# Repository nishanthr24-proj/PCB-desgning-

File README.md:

# PCB-desgning-

Solar battery charge controller designed in KiCad, with green charging and red fault LEDs.

The editable project, local libraries, populated 3D assembly, drawings, BOM, and prototype fabrication files are in **[solar-charger-led-revB/](solar-charger-led-revB/)**.

[Final project report with individual contributions (PDF)](reports/Solar_Charger_RevB_Final_Report.pdf)

## Latest revision: B

Revision B adds an onboard solar-input fuse and series reverse-polarity Schottky diode, nine test points, a shutdown jumper, and corrected VIN_REG labeling. The 4.2 V / 500 mA charging settings and 60 × 55 mm board size are retained.

- [Rev B changes](solar-charger-led-revB/CHANGELOG.md)
- [Staged test plan and expected-versus-measured worksheet](solar-charger-led-revB/TEST_PLAN.md)
- [Earlier Rev A, retained for comparison](solar-charger-led-revA/)

The series diode adds a forward-voltage drop; the fixed input-regulation target remains 17.874 V on the protected charger side. The open/disconnected-NTC limitation remains: monitoring is disabled if its sensor is disconnected. Input protection does not cover reversed battery connections or input overvoltage.

## Open the project

Download or clone this repository, then open [`Solar_Charger_LED_RevB.kicad_pro`](solar-charger-led-revB/Solar_Charger_LED_RevB.kicad_pro) in **KiCad 9 or newer**. Keep the project folder and its local libraries together.

- [Circuit schematic (PDF)](solar-charger-led-revB/previews/Schematic.pdf)
- [Populated PCB preview](solar-charger-led-revB/previews/PCB_3D.png)
- [3D viewing instructions and assembly STEP](solar-charger-led-revB/3D/README.md) — bundled component models; opens in KiCad or FreeCAD
- [Bill of materials](solar-charger-led-revB/BOM.csv)
- [Design details, connector pinouts, and first-power-up instructions](solar-charger-led-revB/README.md)
- [Validation results](solar-charger-led-revB/validation/RESULTS.json)
- [Sources and attribution](solar-charger-led-revB/ATTRIBUTION.md)

## Design target

- One protected 3.7 V nominal lithium-ion 18650 cell, **4.2 V CC/CV** chemistry.
- **500 mA** nominal maximum charging current; the cell must permit this rate.
- Nominal **12 V solar panel**, approximately 18 V at maximum power, **cold open-circuit voltage no greater than 25 V**.
- **LT3652EMSE#PBF in MSOP-12**, with an external 10 kohm / B3380 K battery-temperature sensor.
- Two-layer, 60 × 55 mm PCB with charge/fault LEDs and labeled connectors.

## Validation and prototype status

The revision passes KiCad ERC and PCB DRC with zero violations, zero unconnected items, and zero schematic/PCB mismatches. The exported netlist passes 48 electrical-topology and critical-value checks, and the PCB passes 20 additional probe-layout and check-configuration checks.

The populated 3D model supports presentation and visual inspection of placement, orientation, and connector access. It uses representative component bodies; see the [model notes](solar-charger-led-revB/3D/README.md) before relying on dimensions. This addition changes no circuit routing or fabrication geometry and does not demonstrate charging or LED operation.

**This is an unbuilt engineering prototype.** It has not been fabricated, physically tested, or electrically simulated. Complete the documented bench checks before connecting a lithium-ion cell. J4 status outputs are pulled up to the solar input voltage and must not be connected directly to microcontroller GPIOs.

The design builds on the user-supplied [upstream project](https://github.com/Hirusha785/solar-battery-charge-controller-pcb), whose README credits Fernando S.M.H.G. Attribution and KiCad library license notices are included in the project folder.

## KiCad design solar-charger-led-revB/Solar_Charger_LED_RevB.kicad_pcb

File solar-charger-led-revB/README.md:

# Solar battery charger with charging and fault LEDs — Revision B

Open **Solar_Charger_LED_RevB.kicad_pro** in **KiCad 9 or newer**, then open the
schematic or PCB from the project manager. Extract the complete ZIP first.
The project-local symbol, footprint, and bundled 3D-model libraries use
`${KIPRJMOD}`; no Windows paths or separate library download is required.

## View the populated 3D board

In the PCB Editor, choose **View → 3D Viewer** or press **Alt+3**. Keep the whole
project folder together so the component models in `3dmodels/` load correctly.
For a standalone assembly, open
[`3D/Solar_Charger_LED_RevB_Assembly.step`](3D/Solar_Charger_LED_RevB_Assembly.step)
with **File → Open** in FreeCAD. Presentation images show the
[angled](previews/PCB_3D.png), [top](previews/PCB_3D_Top.png), and
[bottom](previews/PCB_3D_Bottom.png) views.

The assembly includes bodies for all 30 fitted components; the four mounting
holes and nine bare test pads have no separate bodies. The model helps inspect
placement, orientation, and connector access. U1 and L1 use representative bodies;
see [3D/README.md](3D/README.md) for dimensional limits, source information, and
what is included. The LED colors identify D3 and D4; the renders show no operating
state. The 3D addition changes no electrical routing or Gerber geometry.

## Design specification

| Item | Revision B target |
| --- | --- |
| Battery | One **protected 3.7 V nominal Li-ion 18650 cell**, rated by its manufacturer for at least 500 mA charging; 4.2 V CC/CV chemistry only |
| Charging voltage | 4.200 V nominal; actual tolerance includes IC and resistor tolerances |
| Maximum charging current | 500 mA nominal, set by the 0.20 ohm sense resistor |
| Solar panel | Nominal 12 V panel, approximately 18 V at maximum power, at least 5 W recommended |
| Maximum panel open-circuit voltage | **25 V, including the cold-weather Voc increase** |
| Charger-side input regulation | 17.874 V nominal **after D5**; panel-side voltage also includes diode, fuse, and wiring drops; fixed-voltage regulation |
| Charger | LT3652EMSE#PBF, thermally enhanced MSOP-12 |
| PCB | 60 × 55 mm; 2 copper layers; 1.6 mm FR4; 1 oz copper; four M2.5 clearance holes |
| Minimum fabrication geometry | 0.15 mm tracks/clearance; smallest signal vias 0.45 mm diameter / 0.20 mm drill; confirm with your fabricator |
| Temperature sensing | External 10 kohm NTC, B = 3380 K, attached to the cell; approximately 0–40 °C charging window |

Do not connect a LiFePO4 cell, multiple cells in series, a 12 V battery, or an
unidentified battery. A protection circuit and a charger serve different purposes;
this PCB does not replace the protected cell's protection circuit.

## New in Revision B

Revision B builds on the corrected Rev A design and keeps the 4.2 V / 500 mA
charging settings. It adds:

- **F1**, a 1 A replaceable fast-acting 1206 fuse rated at least 32 V DC.
  Verify the chosen part's DC interrupt rating and actual land pattern before purchase.
- **D5**, an SS16-class SMA Schottky diode rated at least 60 V / 1 A, in series
  with the solar input for reverse-polarity blocking.
- **JP1**, a shutdown jumper: closed connects EN/SHDN to GND and disables charging;
  open lets the existing 100 kΩ pull-up enable the charger from protected VIN.
- **Nine labeled test points** for the input stages, battery, current-sense resistor,
  switch node, and ground.
- Corrected **VIN_REG** labeling at J4, replacing the former SET label. The
  open-collector status signals remain VIN-level signals, not MCU-safe logic.

See [CHANGELOG.md](CHANGELOG.md) for the revision history and
[TEST_PLAN.md](TEST_PLAN.md) for staged verification and a measurement worksheet.

## Solar-input protection and limits

The positive input path is:

`J1 pin 1 → VIN_RAW → F1 → VIN_FUSED → D5 → protected VIN → charger and status circuitry`

D5's **anode faces VIN_FUSED; its cathode faces protected VIN**. The original VIN
loads, including the LT3652, input capacitors, input-regulation divider, shutdown
pull-up, and LED circuits, are downstream of D5. J1 pin 2 is the common GND.

The series diode introduces a forward-voltage drop and dissipates `P ≈ I_IN × V_F`.
Its value depends on the selected part, current, and temperature; measure it at
TP2 and TP3. The input-regulation divider is unchanged and senses **protected VIN**.
Thus the nominal panel-side regulation point is **17.874 V + D5 forward drop**,
plus fuse/wiring drops. Check that this suits the actual panel. No exact panel
maximum-power or efficiency claim is made.

F1 provides a sacrificial overcurrent element; it is not resettable. A small panel
may be sufficiently current-limited that it **cannot blow a 1 A fuse during a
short circuit**. Verify the fuse's clearing behavior and interrupt rating against
the actual source. Current limiting remains required for bench tests. Do not
bypass F1 or replace it with a higher rating to make a faulty board run.

These additions do **not** provide input overvoltage/surge protection, battery
reverse-polarity protection, a battery protection circuit, or load management.
Use the specified protected cell, observe battery polarity, and keep input cold
open-circuit voltage at or below 25 V. The NTC-disconnection limitation remains.

## Changes inherited from Revision A

- Added **D3, a green charge LED**, and **D4, a red fault LED**, with current-limiting
  resistors. Indicators run from the panel input rather than draining the battery
  overnight. The open-collector status pull-ups now have a supply connection.
- Connected the LT3652 SENSE and BAT pins to the appropriate sides of R6 and
  connected the battery connector and output capacitors to the charging output.
- Changed R6 to 0.20 ohm for 500 mA rather than the original 0.05 ohm / 2 A setting.
- Replaced the 1N4007 switching/boost diodes with SS14 Schottky diodes and assigned
  a real power-inductor footprint to L1.
- Corrected the precision battery feedback and the panel-voltage divider.
- Added a battery-temperature sensor connector; retained timer termination and
  bad-battery detection.
- Used the pin-equivalent **MSOP LT3652EMSE** variant instead of the original
  0.45 mm-pitch DFN LT3652EDD. The 0.65 mm lead pitch is easier to assemble and
  inspect. **The two IC packages are not footprint-interchangeable.**
- Replaced the onboard unprotected-cell holder, alternative barrel input, and
  uncalibrated potentiometer with clearly labeled terminals and fixed settings.
  Use an external holder suitable for the selected protected cell's length.
- Created a new PCB layout with ground planes, an exposed-pad thermal connection,
  and four thermal vias. Rev A is retained separately for comparison.
- Selected a 22 µF / 16 V 1210 X7R output ceramic capacitor so a suitable part can
  retain at least the required 10 µF effective capacitance under DC bias and tolerance.

## Connectors

| Connector | Pin | Function |
| --- | --- | --- |
| J1 | 1 | Panel positive, VIN_RAW, before F1 and D5 |
| J1 | 2 | Panel negative, GND |
| J2 | 1 | Protected battery positive, BAT+ |
| J2 | 2 | Protected battery negative, GND |
| J3 | 1 | External NTC thermistor |
| J3 | 2 | Other thermistor terminal, GND |
| J4 | 1 | CHRG_N, active-low open-collector status |
| J4 | 2 | FAULT_N, active-low open-collector status |
| J4 | 3 | GND |
| J4 | 4 | VIN_REG analog sense node, approximately 2.7 V at the panel regulation point |

**J4 is not a microcontroller-safe logic interface.** Its two status outputs are
pulled up to protected VIN, potentially close to 25 V. Do not connect them directly
to a GPIO. The VIN_REG pin is a high-impedance analog sense node, not a digital
control input; external
loading changes the panel-regulation voltage. Use a high-impedance meter for checks.

An open/disconnected NTC **disables** the LT3652 temperature-monitoring function;
it is not an open-sensor alarm. Fit and attach the specified sensor before charging
a real cell. Do not replace it with a fixed resistor for battery operation.

## Shutdown jumper and test points

**JP1 open = charging enabled when a suitable solar input is available.**
**JP1 closed = EN/SHDN connected to GND, charging disabled.**
The existing 100 kΩ pull-up limits jumper current to approximately 250 µA at
25 V. Shutdown does not physically disconnect the battery or make the board
safe to rewire. Disconnect input and battery power before changing wiring.

| Test point | Net / location | Intended measurement |
| --- | --- | --- |
| TP1 | VIN_RAW, J1 positive before F1 | Applied panel/bench-supply voltage |
| TP2 | VIN_FUSED, between F1 and D5 | Fuse output and D5 anode voltage |
| TP3 | Protected VIN, after D5 | Charger input and D5 cathode voltage |
| TP4 | BAT, battery/output side | Output voltage relative to ground |
| TP5 | SENSE, R6 pin 1 / inductor side | Positive side of current-sense voltage |
| TP6 | BAT, R6 pin 2 / battery side | Negative side of current-sense voltage |
| TP7 | SW, short branch at the switch node | Switching waveform, using TP8 as nearby ground |
| TP8 | GND_SCOPE, electrically common GND | Short oscilloscope ground connection near TP7 |
| TP9 | GND_BENCH, electrically common GND | Bench meter/supply ground access |

TP4 and TP6 share the BAT net but provide different physical probing locations.
TP8 and TP9 both connect to the common GND net; they are not isolated grounds.
Measure `V(TP5) − V(TP6)` across R6; it is nominally **100 mV at 500 mA**.
Use a meter on its voltage range, or a suitable differential measurement. Never
connect a current-meter input directly between these points or across the battery.
TP5 and TP6 are both above GND. Do not attach an earth-referenced oscilloscope
ground clip to either point. Use a suitable differential probe, or two channels
referenced to board GND with a subtraction measurement, after checking grounding.

Keep the SW connection short. Use a short ground spring to TP8 or a suitable
differential probe, and account for the oscilloscope/supply earth connections.
A long clip-ground loop can distort the waveform or cause an accidental short.
SW probing is optional until the user has suitable equipment and probing practice.

## LED meanings while protected input is present

| Green D3 | Red D4 | Meaning |
| --- | --- | --- |
| On | Off | Charging at or above C/10, approximately 50 mA nominal |
| Off | On | Bad-battery fault / preconditioning timeout |
| On | On | Battery temperature fault; charging paused |
| Off | Off | Standby, shutdown, insufficient solar input, or charging below C/10 |

Both LEDs being off **does not prove that the battery is full**. With timer
termination, charging below C/10 can continue until the timer finishes. The
nominal three-hour timer restarts if the battery has not reached the successful
charge threshold. Low sunlight can reduce charging current and affect completion.

## Electrical calculations

- `I_CHG = 0.100 V / R6 = 0.100 / 0.20 = 0.500 A`.
  With the LT3652 sense-voltage tolerance and a 1% resistor, allow approximately
  470–530 mA at the full-current operating point.
- `P_R6 = I²R = 0.5² × 0.20 = 0.050 W`; use the specified 0.5 W 1206 sense part.
- `V_FLOAT = 3.3 × (1 + R4/R5) = 3.3 × (1 + 60.0k/220k) = 4.200 V`.
- `R3 + (R4 || R5) = 203k + 47.1429k = 250.1429k`, close to the datasheet's
  required 250 kohm input-bias compensation. All three feedback parts are 0.1%.
- `V_IN_REG = 2.7 × (1 + R10/R11) = 2.7 × (1 + 562k/100k) = 17.874 V`
  at TP3 after D5. J1 voltage is higher by the series-path drops.
- `t_TIMER = 0.68 µF × 4.4e6 = 2.992 h`; preconditioning timeout is about 22.4 min.
- L1 is 22 µH. At 25 V input and 4.2 V output, approximate 1 MHz ripple is
  `4.2 × (1 − 4.2/25)/(1e6 × 22e-6) = 0.159 A peak-to-peak`.
  Peak current is approximately 0.58 A at 500 mA charging. Specify Isat ≥1 A and
  Irms ≥0.5 A, including component temperature and tolerance effects.
- With 10 kohm LED resistors, each status pin sinks less than about 2.8 mA at
  25 V, including the 100 kohm pull-up; below the LT3652's 10 mA capability.

These are nominal design calculations, not measurements of assembled hardware.

## Assembly and first power-up

Follow [TEST_PLAN.md](TEST_PLAN.md) in order: component review, unpowered checks,
current-limited no-battery startup, input protection and shutdown, controlled
loaded operation, NTC fault checks, then an attended real-cell test last.
All measurement fields are initially **Not measured**.

Use stencil/paste and controlled reflow for U1, including its exposed ground pad.
Inspect for bridges and verify diode/LED/capacitor polarity. Address thermal-via
solder wicking in the assembly process. F1 is a soldered replaceable fuse, not a
resettable protector. Confirm its and D5's actual component drawings and ratings
before ordering; a generic value or footprint name does not certify a substitute.

A resistor load can check loaded operation, but does not demonstrate battery-charge
taper or termination. Use a battery emulator that can **sink current**, or a
suitable electronic load in constant-voltage mode, for the controlled charging test.
An ordinary source-only bench supply is not a battery emulator.

## Final CAD checks

The prepared Rev B passed ERC with zero errors or warnings and PCB DRC with zero
violations, zero unconnected items, and zero schematic/PCB mismatches. The exported
netlist passed 48 electrical checks; the PCB passed 20 additional probe-layout and
check-configuration checks. Those checks also passed from a separate copied folder.
No ERC rule was set to ignore and no ERC/DRC exclusions were used in this revision.
The 3D checks confirm 30 fitted bodies, local model paths, valid STEP imports,
and unchanged non-model PCB/footprint data and manufacturing files. Run
`python3 validation/check_3d.py` to check the bundle against its recorded evidence.
See `validation/RESULTS.json` and the actual reports. Hardware remains untested.

## Files and validation

- `Solar_Charger_LED_RevB.kicad_pro`, `.kicad_sch`, `.kicad_pcb`: editable project.
- `SolarCharger.kicad_sym`, `SolarCharger.pretty/`, library tables: portable libraries.
- `BOM.csv`: component values, packages, and selection/assembly notes.
- `previews/`: schematic PDF/SVG, assembly drawing, and populated PCB 3D views.
- `3dmodels/`: bundled component STEP models and their `SOURCES.json` manifest.
- `3D/`: standalone board-assembly STEP and viewing/model notes.
- `validation/`: fresh KiCad ERC, PCB DRC, schematic-parity, and connectivity checks.
- `manufacturing/`: prototype plotting/drill outputs if the final geometric checks pass.
- `ATTRIBUTION.md`: upstream project, reference documents, and library information.
- `CHANGELOG.md`: Rev B additions and Rev A lineage.
- `TEST_PLAN.md`: CAD-check criteria, staged bench procedure, and blank results table.

No manufacturer simulation model was used for Rev B, and no simulation is included
in this revision. The board has **not** been fabricated, powered, or physically
validated here. ERC/DRC and connectivity checks establish CAD consistency and
geometry only. Analog stability, efficiency, thermal performance, transient
behavior, EMC, and actual battery charging still require bench verification.

## Presentation summary

“Our Rev B keeps the single-cell 4.2 V / 500 mA charger and its charging/fault
indicators. We added a fused reverse-polarity input path, dedicated measurement
points, a shutdown jumper, and clearer signal labeling. The changes make controlled
testing more convenient. A populated 3D assembly illustrates component placement
and connector access. The CAD reports document design-rule and connectivity
checks; physical charging, thermal, and protection performance remain to be measured.”

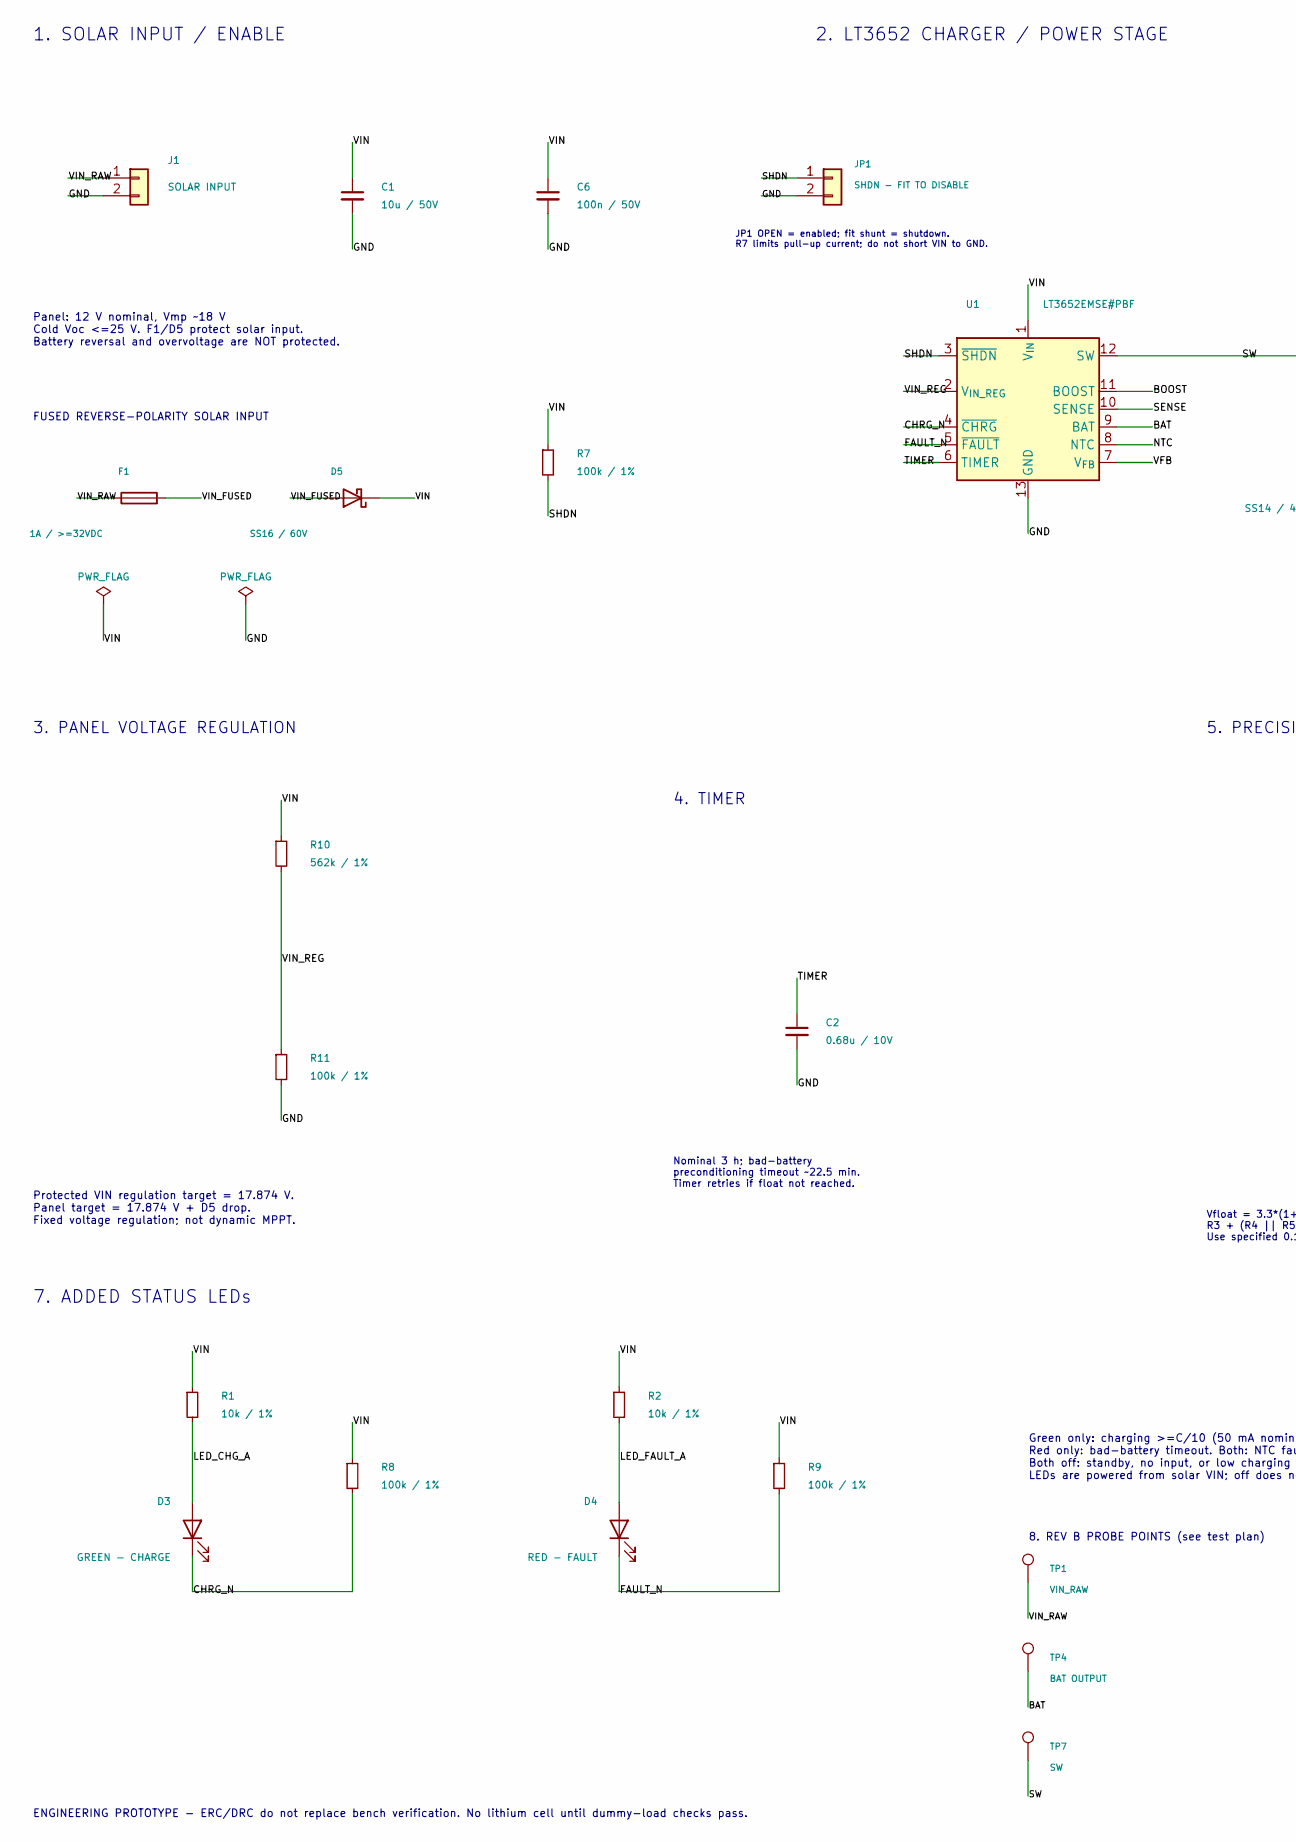
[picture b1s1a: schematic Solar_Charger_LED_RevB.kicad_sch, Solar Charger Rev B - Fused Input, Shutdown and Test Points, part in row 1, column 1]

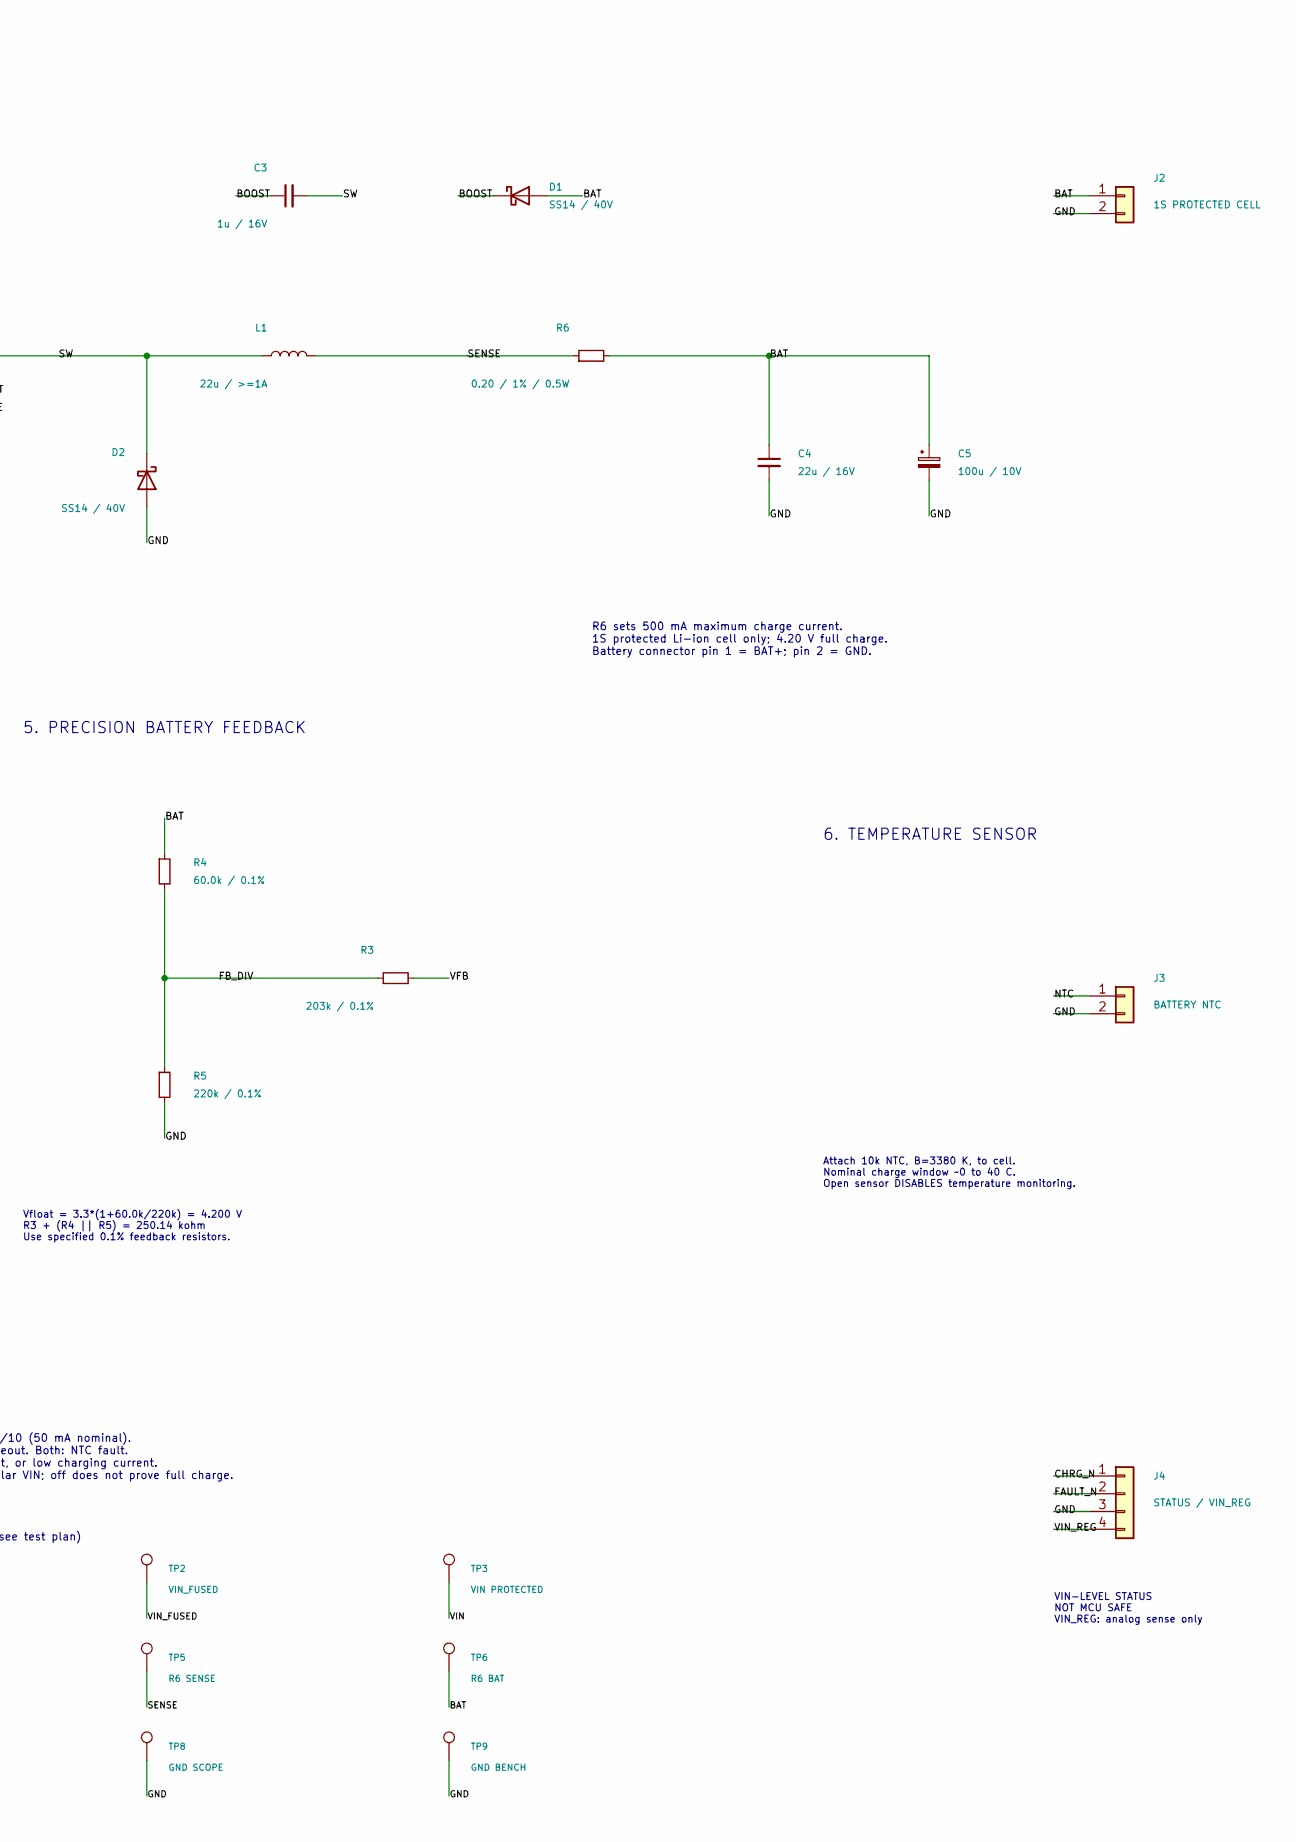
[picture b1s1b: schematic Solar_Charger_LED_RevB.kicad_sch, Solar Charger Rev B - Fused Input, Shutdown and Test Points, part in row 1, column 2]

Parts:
C1: 10u / 50V; C_1210_3225Metric
C2: 0.68u / 10V; C_0805_2012Metric
C3: 1u / 16V; C_0805_2012Metric
C4: 22u / 16V; C_1210_3225Metric
C5: 100u / 10V; CP_Radial_D6.3mm_P2.50mm
C6: 100n / 50V; C_0805_2012Metric
D1, D2: SS14 / 40V; D_SMA; MPN SS14
D3: GREEN - CHARGE; LED_0805_2012Metric
D4: RED - FAULT; LED_0805_2012Metric
D5: SS16 / 60V; D_SMA; MPN SS16 (SMA, verify vendor datasheet)
F1: 1A / >=32VDC; Fuse_1206_3216Metric
J1: SOLAR INPUT; TerminalBlock_Phoenix_MKDS-1,5-2-5.08_1x02_P5.08mm_Horizont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
J2: 1S PROTECTED CELL; TerminalBlock_Phoenix_MKDS-1,5-2-5.08_1x02_P5.08mm_Horizont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
J3: BATTERY NTC; PinHeader_1x02_P2.54mm_Vertical
J4: STATUS / VIN_REG; PinHeader_1x04_P2.54mm_Vertical
JP1: SHDN - FIT TO DISABLE; PinHeader_1x02_P2.54mm_Vertical
L1: 22u / >=1A; L_Bourns-SRN6028; MPN SRN6028-220M
R1, R2: 10k / 1%; R_0805_2012Metric
R3: 203k / 0.1%; R_0805_2012Metric
R4: 60.0k / 0.1%; R_0805_2012Metric
R5: 220k / 0.1%; R_0805_2012Metric
R6: 0.20 / 1% / 0.5W; R_1206_3216Metric
R7, R8, R9, R11: 100k / 1%; R_0805_2012Metric
R10: 562k / 1%; R_0805_2012Metric
TP1: VIN_RAW; TestPoint_Pad_D1.5mm
TP2: VIN_FUSED; TestPoint_Pad_D1.5mm
TP3: VIN PROTECTED; TestPoint_Pad_D1.5mm
TP4: BAT OUTPUT; TestPoint_Pad_D1.5mm
TP5: R6 SENSE; TestPoint_Pad_D1.0mm
TP6: R6 BAT; TestPoint_Pad_D1.0mm
TP7: SW; ProbePad_D0.8mm
TP8: GND SCOPE; ProbePad_D0.8mm
TP9: GND BENCH; TestPoint_Pad_D1.5mm
U1: LT3652EMSE#PBF; MSOP-12-1EP_3x4.039mm_P0.65mm_EP1.651x2.845mm; MPN LT3652EMSE#PBF

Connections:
/BAT: C4.1, C5.1, D1.2 (A), J2.1, R4.1, R6.2, TP4.1, TP6.1, U1.9 (BAT)
/BOOST: C3.1, D1.1 (K), U1.11 (BOOST)
/CHRG_N: D3.1 (K), J4.1, R8.2, U1.4 (~CHRG)
/FAULT_N: D4.1 (K), J4.2, R9.2, U1.5 (~FAULT)
/FB_DIV: R3.1, R4.2, R5.1
/GND: C1.2, C2.2, C4.2, C5.2, C6.2, D2.2 (A), J1.2, J2.2, J3.2, J4.3, JP1.2, R5.2, R11.2, TP8.1, TP9.1, U1.13 (GND)
/LED_CHG_A: D3.2 (A), R1.2
/LED_FAULT_A: D4.2 (A), R2.2
/NTC: J3.1, U1.8 (NTC)
/SENSE: L1.2, R6.1, TP5.1, U1.10 (SENSE)
/SHDN: JP1.1, R7.2, U1.3 (~SHDN)
/SW: C3.2, D2.1 (K), L1.1, TP7.1, U1.12 (SW)
/TIMER: C2.1, U1.6 (TIMER)
/VFB: R3.2, U1.7 (V_{FB})
/VIN: C1.1, C6.1, D5.1 (K), R1.1, R2.1, R7.1, R8.1, R9.1, R10.1, TP3.1, U1.1 (V_{IN})
/VIN_FUSED: D5.2 (A), F1.2, TP2.1
/VIN_RAW: F1.1, J1.1, TP1.1
/VIN_REG: J4.4, R10.2, R11.1, U1.2 (V_{IN_REG})

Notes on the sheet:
1. SOLAR INPUT / ENABLE
Panel: 12 V nominal, Vmp ~18 V Cold Voc <=25 V. F1/D5 protect solar input. Battery reversal and overvoltage are NOT protected.
2. LT3652 CHARGER / POWER STAGE
R6 sets 500 mA maximum charge current. 1S protected Li-ion cell only; 4.20 V full charge. Battery connector pin 1 = BAT+; pin 2 = GND.
3. PANEL VOLTAGE REGULATION
Protected VIN regulation target = 17.874 V. Panel target = 17.874 V + D5 drop. Fixed voltage regulation; not dynamic MPPT.
4. TIMER
Nominal 3 h; bad-battery preconditioning timeout ~22.5 min. Timer retries if float not reached.
5. PRECISION BATTERY FEEDBACK
Vfloat = 3.3*(1+60.0k/220k) = 4.200 V R3 + (R4 || R5) = 250.14 kohm Use specified 0.1% feedback resistors.
6. TEMPERATURE SENSOR
Attach 10k NTC, B=3380 K, to cell. Nominal charge window ~0 to 40 C. Open sensor DISABLES temperature monitoring.
7. ADDED STATUS LEDs
Green only: charging >=C/10 (50 mA nominal). Red only: bad-battery timeout. Both: NTC fault. Both off: standby, no input, or low charging current. LEDs are powered from solar VIN; off does not prove full charge.
VIN-LEVEL STATUS NOT MCU SAFE VIN_REG: analog sense only
ENGINEERING PROTOTYPE - ERC/DRC do not replace bench verification. No lithium cell until dummy-load checks pass.
FUSED REVERSE-POLARITY SOLAR INPUT
JP1 OPEN = enabled; fit shunt = shutdown. R7 limits pull-up current; do not short VIN to GND.
8. REV B PROBE POINTS (see test plan)

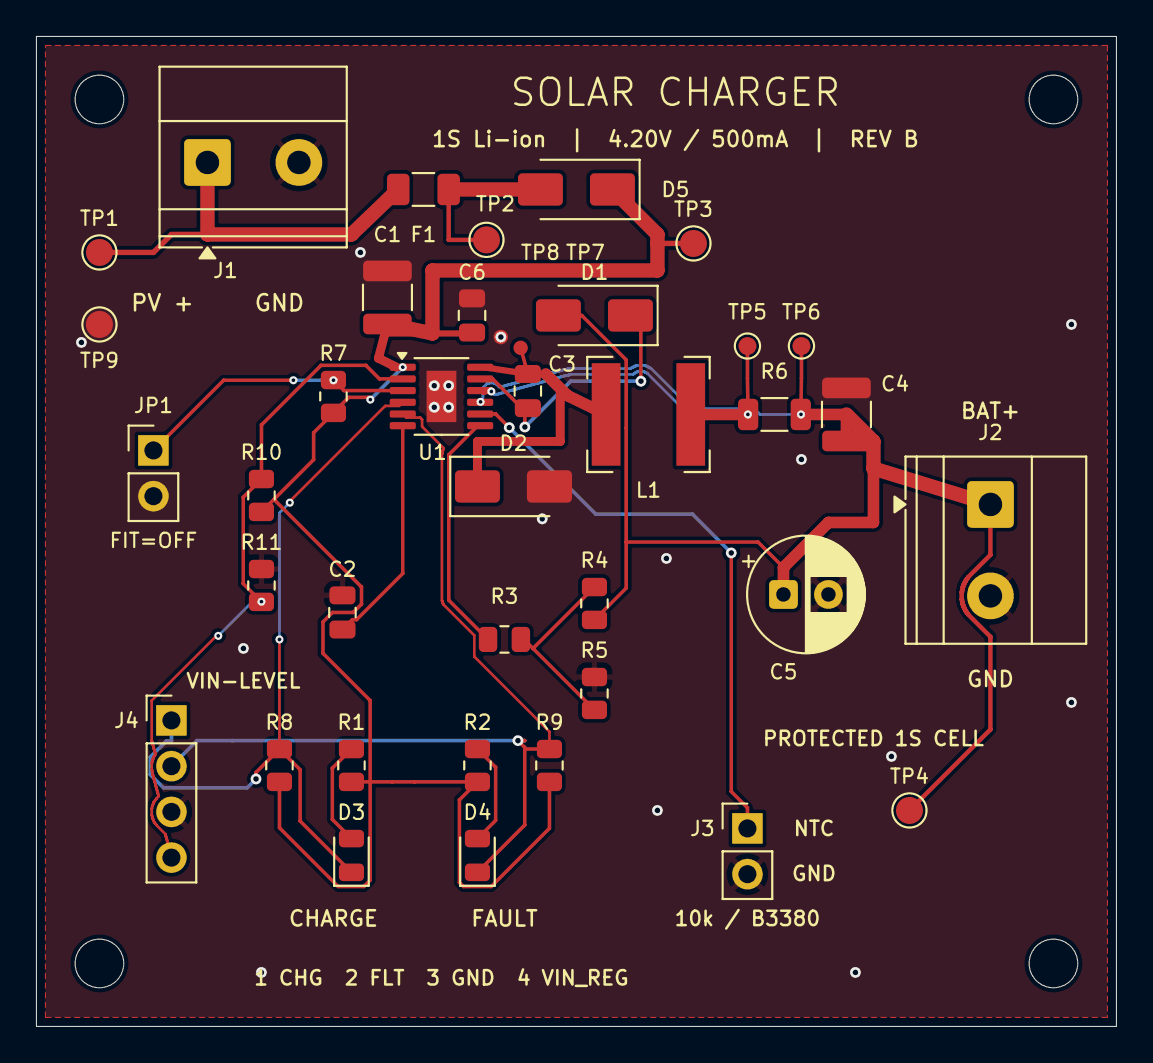
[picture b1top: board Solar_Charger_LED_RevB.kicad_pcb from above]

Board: 2 copper layers, 60.0 x 55.0 mm, 43 parts (0 on the bottom side), 18 nets.

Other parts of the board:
H1, H2, H3, H4: MountingHole_2.7mm_M2.5

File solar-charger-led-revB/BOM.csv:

Reference,Quantity,Value,Footprint,Suggested MPN (verify availability),Selection / assembly notes
U1,1,LT3652EMSE#PBF,SolarCharger:MSOP-12-1EP_3x4.039mm_P0.65mm_EP1.651x2.845mm,LT3652EMSE#PBF,Pin-equivalent MSOP variant has wider 0.65mm pitch. Exposed pad must be soldered to GND; use reflow.
J1,1,SOLAR INPUT,"SolarCharger:TerminalBlock_Phoenix_MKDS-1,5-2-5.08_1x02_P5.08mm_Horizontal",,Raw solar connector before F1/D5; panel cold Voc<=25V.
J2,1,1S PROTECTED CELL,"SolarCharger:TerminalBlock_Phoenix_MKDS-1,5-2-5.08_1x02_P5.08mm_Horizontal",,"External protected 18650, 4.2 V CC/CV; pin 1 BAT+, pin 2 GND."
J3,1,BATTERY NTC,SolarCharger:PinHeader_1x02_P2.54mm_Vertical,,External 10k NTC B=3380K; attach to cell. Open sensor disables temperature protection.
J4,1,STATUS / VIN_REG,SolarCharger:PinHeader_1x04_P2.54mm_Vertical,,"VIN-level CHRG/FAULT, not MCU safe; pin4 VIN_REG sense only."
C1,1,10u / 50V,SolarCharger:C_1210_3225Metric,,X7R; check effective capacitance at 25V bias.
C2,1,0.68u / 10V,SolarCharger:C_0805_2012Metric,,"X7R, low leakage; nominal 3 hour timer; retries if not near float."
C3,1,1u / 16V,SolarCharger:C_0805_2012Metric,,X7R bootstrap capacitor; 16V rating is across BOOST to SW.
C4,1,22u / 16V,SolarCharger:C_1210_3225Metric,,X7R output bypass; choose a part with >=10uF effective capacitance at 4.2V over temperature/tolerance.
C5,1,100u / 10V,SolarCharger:CP_Radial_D6.3mm_P2.50mm,,"Low ESR, non-ceramic, 100uF, >=10V; verify 6.3mm diameter and 2.50mm lead pitch against chosen part."
C6,1,100n / 50V,SolarCharger:C_0805_2012Metric,,X7R local high-frequency input bypass.
D1,1,SS14 / 40V,SolarCharger:D_SMA,SS14,"Bootstrap refresh Schottky; cathode BOOST, anode BAT."
D2,1,SS14 / 40V,SolarCharger:D_SMA,SS14,"Catch Schottky, 1A / 40V minimum; cathode SW, anode GND."
L1,1,22u / >=1A,SolarCharger:L_Bourns-SRN6028,SRN6028-220M,"Shielded power inductor; Isat>=1A, Irms>=0.5A, low DCR; Bourns SRN6028-220M."
R1,1,10k / 1%,SolarCharger:R_0805_2012Metric,,0.125W or better; LED current approx 1.5mA at VIN=18V.
R2,1,10k / 1%,SolarCharger:R_0805_2012Metric,,0.125W or better; limits fault LED current.
D3,1,GREEN - CHARGE,SolarCharger:LED_0805_2012Metric,,"Green, low-current LED; cathode to CHRG_N."
D4,1,RED - FAULT,SolarCharger:LED_0805_2012Metric,,"Red, low-current LED; cathode to FAULT_N."
R3,1,203k / 0.1%,SolarCharger:R_0805_2012Metric,,Bias compensation: R3+(R4||R5)=250.14kohm.
R4,1,60.0k / 0.1%,SolarCharger:R_0805_2012Metric,,Feedback top resistor; do not substitute 60.4k without recalculation.
R5,1,220k / 0.1%,SolarCharger:R_0805_2012Metric,,Feedback lower resistor; nominal Vfloat = 3.3*(1+60/220)=4.200V.
R6,1,0.20 / 1% / 0.5W,SolarCharger:R_1206_3216Metric,,Current sense; Kelvin route both terminals; Imax=0.1/0.20=0.50A; P=0.05W.
R7,1,100k / 1%,SolarCharger:R_0805_2012Metric,,100k protected-VIN pull-up to SHDN; JP1 to GND disables charging.
R8,1,100k / 1%,SolarCharger:R_0805_2012Metric,,Open-collector pull-up to VIN; not an MCU-level interface.
R9,1,100k / 1%,SolarCharger:R_0805_2012Metric,,Open-collector pull-up to VIN; not an MCU-level interface.
R10,1,562k / 1%,SolarCharger:R_0805_2012Metric,,"Input-voltage regulation top; target approx17.87V, not dynamic perturb-and-observe MPPT."
R11,1,100k / 1%,SolarCharger:R_0805_2012Metric,,Input-voltage regulation bottom; 2.7*(1+562/100)=17.874V.
NTC_EXTERNAL,1,10k at 25C / B3380K,"External, attach to battery",,Required for temperature monitoring; disconnected sensor disables this function.
BATTERY_EXTERNAL,1,1S protected Li-ion 18650 / 4.2V CC-CV,External suitable holder,,Manufacturer must permit >=500mA charging. Observe polarity.
PANEL_EXTERNAL,1,12V nominal / Vmp approx18V / cold Voc<=25V,External,,At least 5W recommended.
FUSE_EXTERNAL,1,Appropriate battery-lead fuse,External PV and battery leads,,External battery lead protection still required; onboard F1 protects the solar input path only.
F1,1,1A / >=32VDC,SolarCharger:Fuse_1206_3216Metric,,"Fast acting replaceable DC fuse; >=32VDC, verify DC interruption rating and exact 1206 land pattern. A current-limited panel may not blow this fuse."
D5,1,SS16 / 60V,SolarCharger:D_SMA,"SS16 (SMA, verify vendor datasheet)","Series input reverse-polarity diode: anode VIN_FUSED, cathode protected VIN; >=1A, >=60V. No overvoltage or battery-reversal protection."
JP1,1,SHDN - FIT TO DISABLE,SolarCharger:PinHeader_1x02_P2.54mm_Vertical,,Normally OPEN: enabled by R7 100k pull-up to protected VIN. Fit 2.54mm shunt to ground SHDN and disable charging. Never bridge VIN directly to ground.
TP1,0,VIN_RAW,SolarCharger:TestPoint_Pad_D1.5mm,,"Raw panel voltage, BEFORE F1; probe only. Fabricated probe pad, no component to fit."
TP2,0,VIN_FUSED,SolarCharger:TestPoint_Pad_D1.5mm,,"After F1 and before D5; probe only. Fabricated probe pad, no component to fit."
TP3,0,VIN PROTECTED,SolarCharger:TestPoint_Pad_D1.5mm,,"Protected charger supply, after F1 and D5; probe only. Fabricated probe pad, no component to fit."
TP4,0,BAT OUTPUT,SolarCharger:TestPoint_Pad_D1.5mm,,"Battery output voltage; use J2 for a load, not this probe stub. Fabricated probe pad, no component to fit."
TP5,0,R6 SENSE,SolarCharger:TestPoint_Pad_D1.0mm,,"R6 pin1 Kelvin probe, SENSE / inductor side; not a power path. Fabricated probe pad, no component to fit."
TP6,0,R6 BAT,SolarCharger:TestPoint_Pad_D1.0mm,,"R6 pin2 Kelvin probe, BAT / battery side; nominal TP5-TP6=100mV at 500mA. Fabricated probe pad, no component to fit."
TP7,0,SW,SolarCharger:ProbePad_D0.8mm,,"Small 0.8mm SW probe pad; short stub to local switching node. Short ground spring to TP8 only after checking scope grounding. Fabricated probe pad, no component to fit."
TP8,0,GND SCOPE,SolarCharger:ProbePad_D0.8mm,,"Nearby SW probe ground. Ground is common, not isolated. Fabricated probe pad, no component to fit."
TP9,0,GND BENCH,SolarCharger:TestPoint_Pad_D1.5mm,,"Bench-meter ground reference. Fabricated probe pad, no component to fit."
SHUNT_JP1,1,2.54mm 2-pin jumper shunt,External accessory,,Leave OFF JP1 during normal charging; fit to disable.
